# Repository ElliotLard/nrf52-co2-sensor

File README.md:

# nrf52-co2-sensor

BLE-based smart home compatible CO₂ sensor built around the **nRF52840 (via MDBT50Q module)** and the **Sensirion SCD30 NDIR CO₂ sensor**.

The device measures indoor CO₂ concentration and transmits readings wirelessly using **Bluetooth Low Energy (BLE)** for integration with smart home systems or mobile applications.

This project includes:

- Custom **schematic design**
- **PCB layout** in KiCad
- **BLE communication**
- Sensor integration using **I²C**

---

# Project Status

**Current Status (30 July 2026)**
- Rev A Board has been printed and assembled
---
#Front

#Back

# Hardware Design

## Schematic (Rev A)

## PCB Layout (Rev A)

---

# Design Goals

- Accurate CO₂ measurement
- Wireless communication via **Bluetooth Low Energy**
- USB-C powered device
- Smart home compatibility

---

# Major Components

## MCU + BLE

**MDBT50Q-1MV2**  
Contains **Nordic nRF52840 BLE microcontroller**

---

## CO₂ Sensor

**Sensirion SCD30**

NDIR-based CO₂ sensor with integrated temperature and humidity measurement.

---

## USB-C Receptacle

**USB4105-GF-A**

Used for power and optional USB communication/debugging.

---

<!---
Future updates:

- Rev B schematic
- PCB layout screenshots
- Fabricated board photos

---
-->
# Firmware

*(Placeholder — firmware development will begin after PCB assembly)*

Planned features:

- I²C communication with SCD30
- CO₂ measurement acquisition
- BLE data transmission
- Low power operation

---

# Tools Used

- **KiCad** — schematic and PCB design
- **Git / GitHub** — version control
- **Datasheets and reference designs** from component manufacturers

---

# Future Work

- BLE data integration with **Home Assistant**
- Explore possibility of Battery-powered variant
- Compact enclosure design
- Airflow optimization for accurate sensing

---

<!---
# License

*(Placeholder — consider adding MIT or Apache license)*
-->

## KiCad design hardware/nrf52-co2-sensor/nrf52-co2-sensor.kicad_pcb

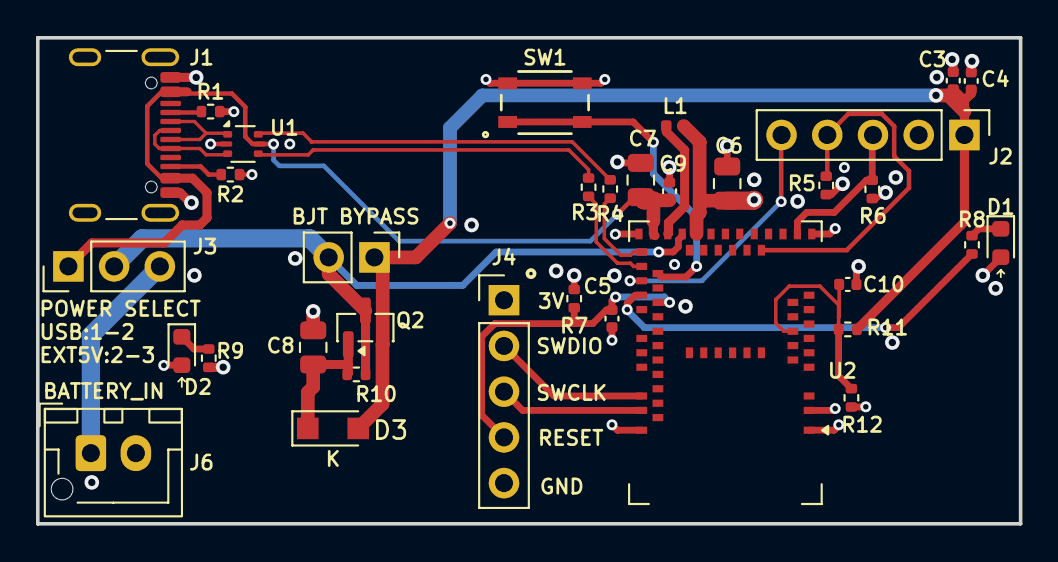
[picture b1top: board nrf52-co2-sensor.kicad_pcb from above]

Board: 4 copper layers, 54.6 x 27.0 mm, 34 parts (0 on the bottom side), 27 nets.

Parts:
C3: 2.2uf; C_0402_1005Metric
C4, C9: 0.1uf; C_0402_1005Metric
C5: 100nF; C_0402_1005Metric
C6, C7: 10uf; C_0805_2012Metric
C8: 47uf; C_0805_2012Metric
C10: 10nf; C_0402_1005Metric
D1, D2: LED; LED_0603_1608Metric
D3: 1N914; Nexperia_CFP3_SOD-123W
J1: USB4105-GF-A; USB_C_Receptacle_GCT_USB4105-xx-A_16P_TopMnt_Horizontal
J2: SCD30; PinHeader_1x05_P2.54mm_Vertical
J3: Conn_01x03; PinHeader_1x03_P2.54mm_Vertical
J4: SWD; PinHeader_1x05_P2.54mm_Vertical
J6: Conn_01x02; JST_XH_B2B-XH-AM_1x02_P2.50mm_Vertical
J7: Conn_01x02; PinHeader_1x02_P2.54mm_Vertical
L1: 10uH; L_0402_1005Metric
Q2: Q_NPN_BEC; SOT-23
R1, R2: 5.1k; R_0402_1005Metric
R3, R4: 22; R_0402_1005Metric
R5, R6, R9: 4.7k; R_0402_1005Metric
R7: 10k; R_0402_1005Metric
R8: 2.2k; R_0402_1005Metric
R10: 150; R_0402_1005Metric
R11: 2.2M; R_0402_1005Metric
R12: 1M; R_0402_1005Metric
SW1: SW_Push; SW4_SKRPABE010_ALPS
U1: USBLC6-2P6; SOT-666
U2: MDBT50Q-1MV2; Raytac_MDBT50Q

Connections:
/3V_VDD: C6.2, D1.2 (A), D2.2 (A), J4.1, L1.1, R5.2, R6.2, R7.2, U2.28 (VDD)
/BASE: C8.2, D3.1 (K), Q2.1 (B), R10.1
/BUTTON_1: SW1.1, SW1.2, U2.36 (P0.14)
/CC1: J1.A5 (CC1), R1.1
/CC2: J1.B5 (CC2), R2.1
/D1+: R3.2, U1.4 (I/O2)
/D1-: R4.1, U1.6 (I/O1)
/D+: J1.A6 (D+), J1.B6 (D+), U1.3 (I/O2)
/D-: J1.A7 (D-), J1.B7 (D-), U1.1 (I/O1)
/DCCH: L1.2, U2.31 (DCCH)
/D_MCU+: R3.1, U2.35 (D+)
/D_MCU-: R4.2, U2.34 (D-)
/External Power: J3.3, J6.1
/LED_1: R8.2, U2.39 (P0.15)
/POWER_ADC: C10.2, R11.2, R12.1, U2.9 (P0.03/AINI)
/POWER_RAW: J3.2, J7.2, Q2.3 (C), R10.2, U2.30 (VDDH)
/POWER_SENS: C3.1, C4.1, D3.2 (A), J2.1, J7.1, Q2.2 (E), R11.1
/RESETN: C5.2, J4.4, R7.1, U2.40 (RESETN)
/SCD30_RDY: J2.5, U2.37 (P0.13)
/SCD30_SCL: J2.3, R6.1, U2.16 (P0.27)
/SCD30_SDA: J2.4, R5.1, U2.19 (P0.26)
/SWCLK: J4.3, U2.53 (SWDCLK)
/SWDIO: J4.2, U2.51 (SWDIO)
/VBUS: C7.2, C9.1, J1.A4 (VBUS), J1.A9 (VBUS), J1.B4 (VBUS), J1.B9 (VBUS), J3.1, U1.5 (VBUS), U2.32 (VBUS)
GND: C3.2, C4.2, C5.1, C6.1, C7.1, C8.1, C9.2, C10.1, J1.A1 (GND), J1.A12 (GND), J1.B1 (GND), J1.B12 (GND), J2.2, J4.5, J6.2, R1.2, R2.2, R9.2, R12.2, SW1.3, SW1.4, U1.2 (GND), U2.1 (GND), U2.2 (GND), U2.15 (GND), U2.33 (GND), U2.55 (GND)
unnamed: D1.1 (K), R8.1
unnamed: D2.1 (K), R9.1

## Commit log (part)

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2026-02-08 Add initial project folder structure
2026-02-08 added datasheet, start of kicad project
2026-02-15 Finished revision 1 of schematic passed ERC and ready for review
2026-02-16 Added data lines for usb connectivity to MDBT50Q
2026-02-16 added jumper in front of LDO
2026-02-16 changed one of the LED's to always-on and increased resistor values for both LED's to 10k for always-on and 6.8k for GPIO
2026-02-16 Added 0.1uF decoupling on VDD, last commit before PCB Layout
2026-02-18 Removed external pullups on I2C, decided they were unnecessary for 100khz with the internals. Also removed redundant caps on the side of LOD, but left the ones on the side of the MCU.
2026-03-02 changed usb-c component and rewired with an ESD diode. Also started choosing other components and footprints.
2026-03-02 added external pullups back in for i2c
2026-03-05 Update README.md
    Improved readme
2026-03-05 finished assigning footprints, chose LEDs and button, assigned 4.7k resistors to I2C pullups and also to LED's. Passed ERC, usb_D- and + were not connected properly and fixed that as well
2026-03-06 Started preliminary pcb component placement. Switched JST for header. also switched pushbutton component for a smaller footprint.
2026-03-07 Last commit before power rework
2026-03-07 reworked power to remove LDO and work directly from USB
2026-03-07 fix folder structure
2026-03-09 first iteration of pcb layout ready for review
2026-03-09 Update README.md
    Updated readme with current project status
2026-06-01 Changes made to schematic. BJT Lowpass filter, jumper for power measurement/choosing battery vs usb power, removal of redundant capacitors, and other additional fixes.
2026-06-02 Finished PCB Layout and BOM read for review
